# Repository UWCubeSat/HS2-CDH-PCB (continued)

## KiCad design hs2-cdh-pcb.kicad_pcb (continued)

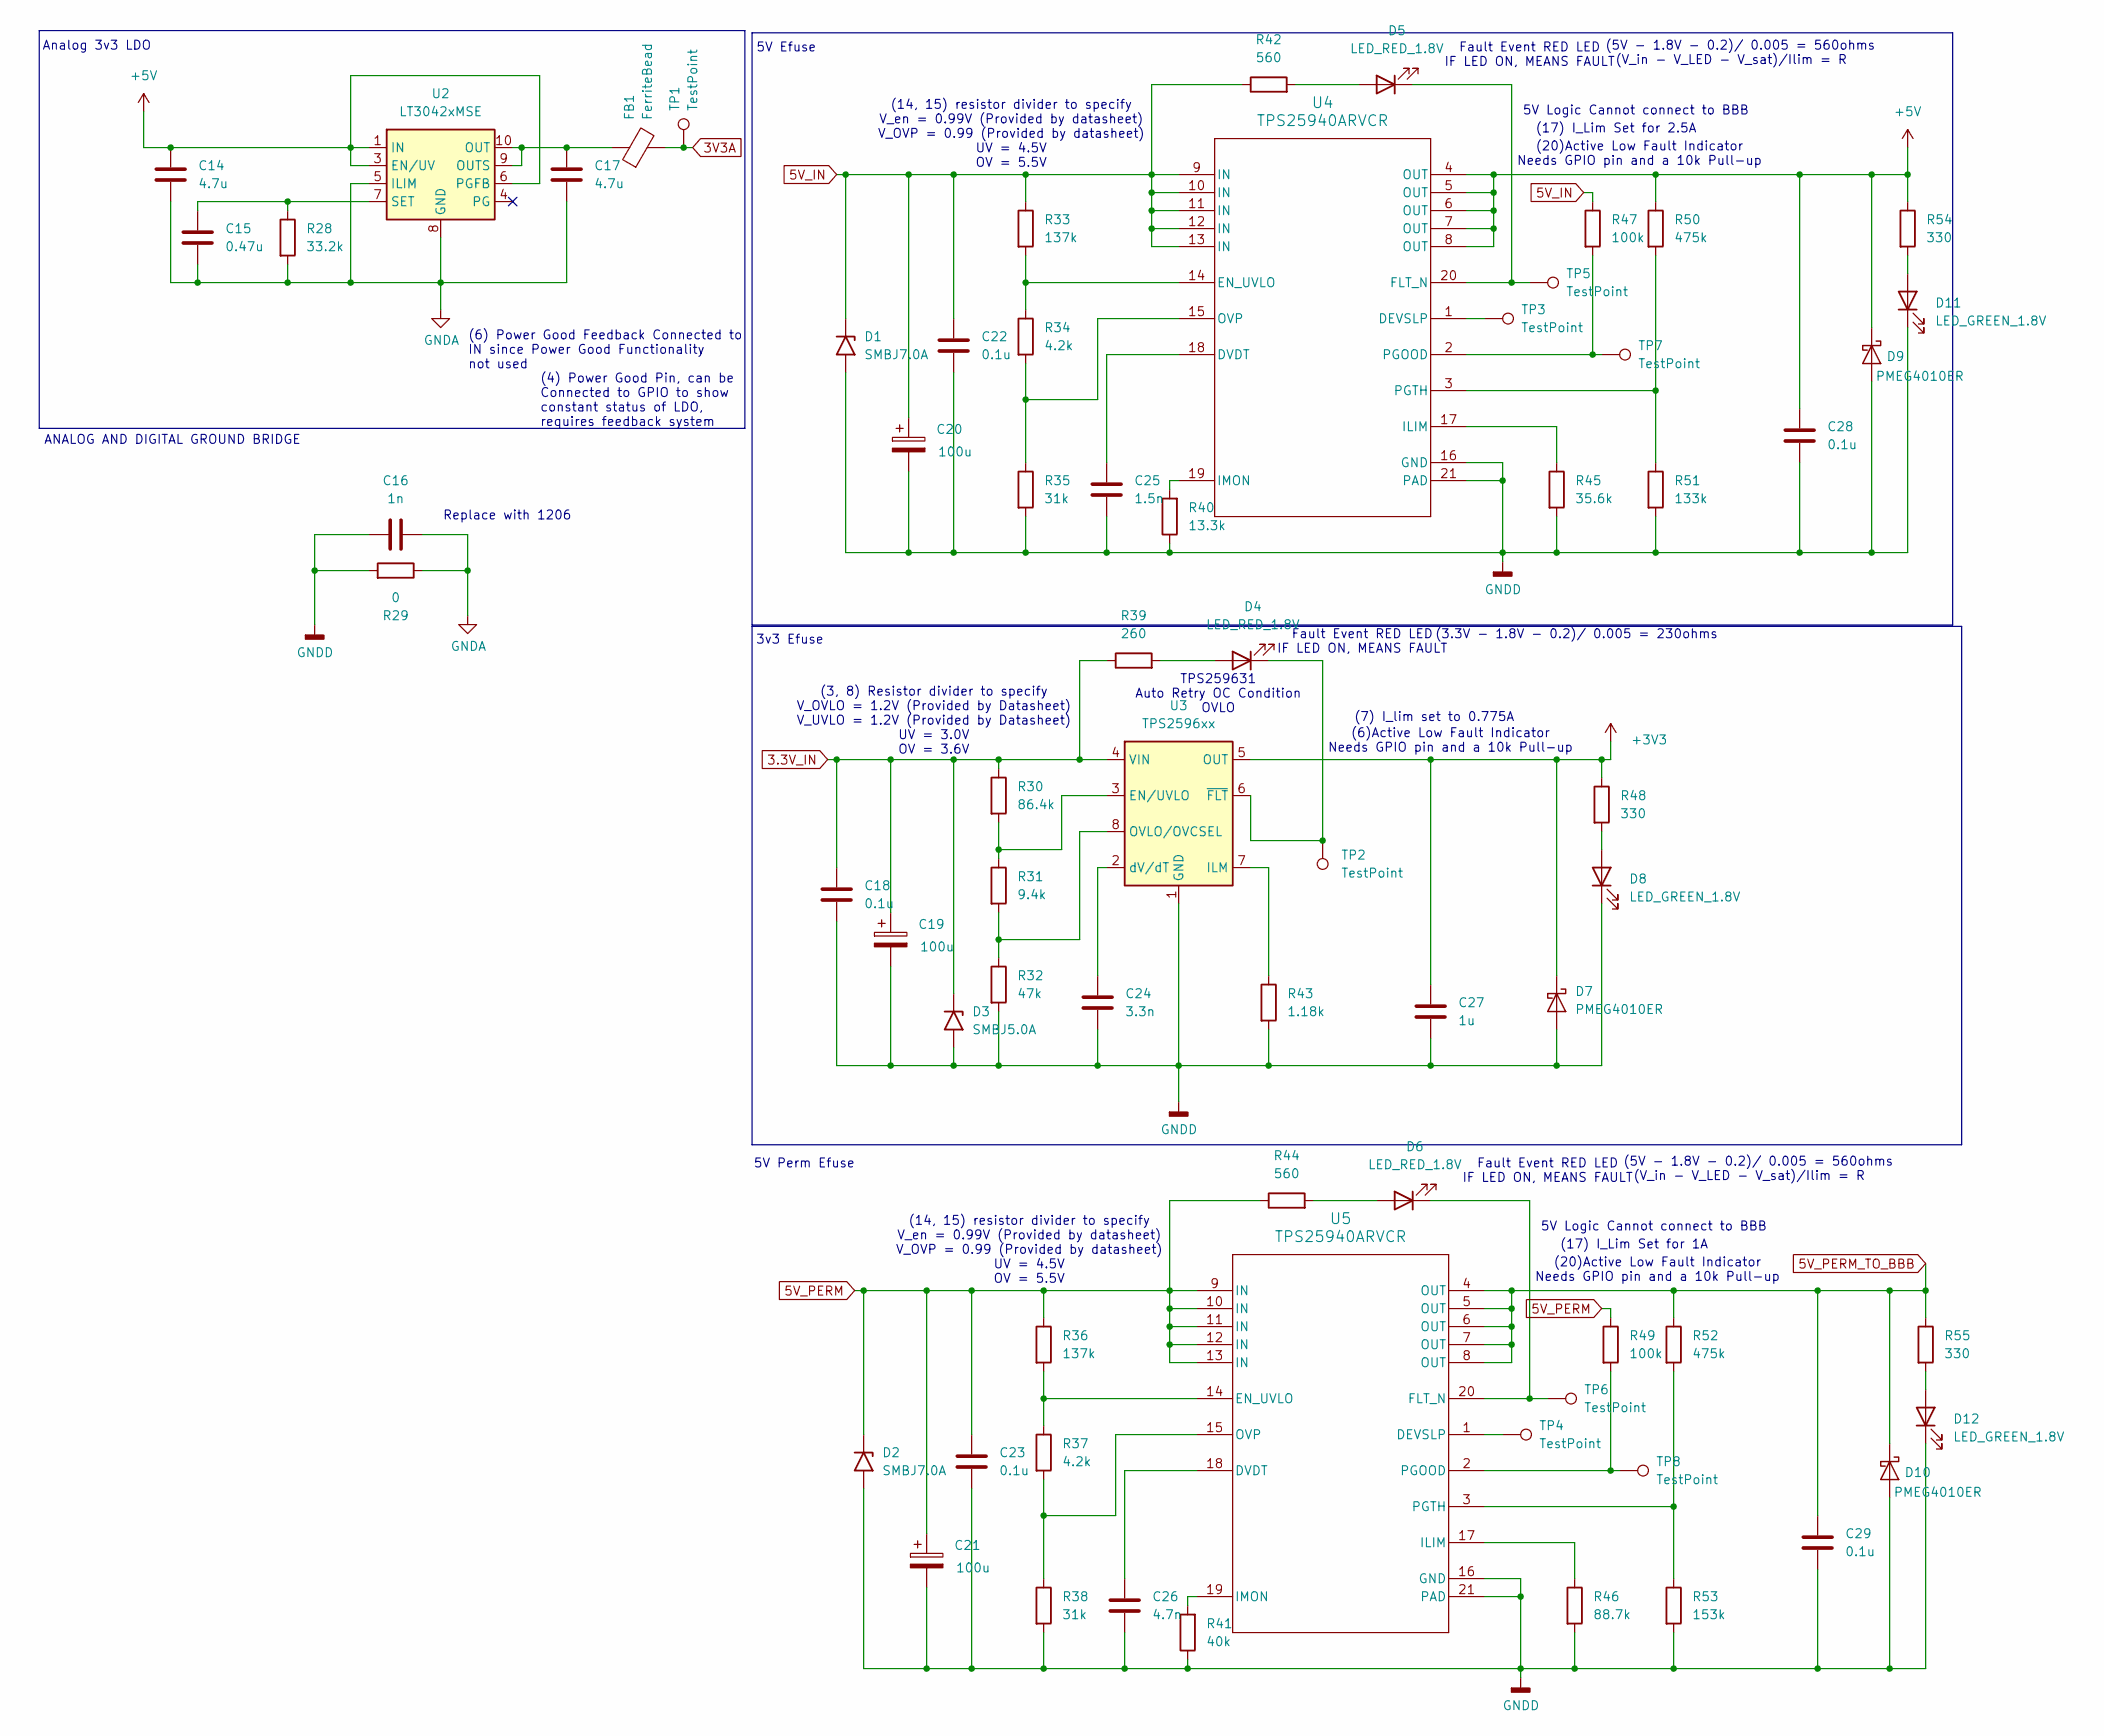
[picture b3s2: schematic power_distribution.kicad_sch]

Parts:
C14, C17: 4.7u; C_0603_1608Metric
C15: 0.47u; C_0603_1608Metric
C16: 1n; C_1206_3216Metric
C18, C22, C23, C28, C29: 0.1u; C_0603_1608Metric
C19, C20, C21: 100u; CAPMP7.6X4.3_1.9N_KEM
C24: 3.3n; C_0603_1608Metric
C25: 1.5n; C_0603_1608Metric
C26: 4.7n; C_0603_1608Metric
C27: 1u; C_0603_1608Metric
D1, D2: SMBJ7.0A; D_SMA
D3: SMBJ5.0A; D_SMA
D4, D5, D6: LED_RED_1.8V; LED_0603_1608Metric
D7, D9, D10: PMEG4010ER; Nexperia_CFP3_SOD-123W
D8, D11, D12: LED_GREEN_1.8V; LED_0603_1608Metric
FB1: FerriteBead; L_0603_1608Metric
R28: 33.2k; R_0603_1608Metric
R29: 0; R_1206_3216Metric
R30: 86.4k; R_0603_1608Metric
R31: 9.4k; R_0603_1608Metric
R32: 47k; R_0603_1608Metric
R33, R36: 137k; R_0603_1608Metric
R34, R37: 4.2k; R_0603_1608Metric
R35, R38: 31k; R_0603_1608Metric
R39: 260; R_0603_1608Metric
R40: 13.3k; R_0603_1608Metric
R41: 40k; R_0603_1608Metric
R42, R44: 560; R_0603_1608Metric
R43: 1.18k; R_0603_1608Metric
R45: 35.6k; R_0603_1608Metric
R46: 88.7k; R_0603_1608Metric
R47, R49: 100k; R_0603_1608Metric
R48, R54, R55: 330; R_0603_1608Metric
R50, R52: 475k; R_0603_1608Metric
R51: 133k; R_0603_1608Metric
R53: 153k; R_0603_1608Metric
TP1, TP2, TP3, TP4, TP5, TP6, TP7, TP8: TestPoint; TestPoint_Pad_D1.0mm
U2: LT3042xMSE; MSOP-10-1EP_3x3mm_P0.5mm_EP1.68x1.88mm
U3: TPS2596xx; TI_SO-PowerPAD-8_ThermalVias
U4, U5: TPS25940ARVCR; Texas_RVC0020A_WQFN-20-1EP_3x4mm_P0.5mm_EP1.6x2.6mm

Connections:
3.3V_IN: C18.1, C19.1, D3.1 (A1), R30.1, R39.1, U3.4 (VIN); also elsewhere on the board
3V3A: FB1.2, TP1.1 (1_1); also elsewhere on the board
5V_IN: C20.1, C22.1, D1.1 (A1), R33.1, R42.1, R47.1, U4.9 (IN), U4.10 (IN), U4.11 (IN), U4.12 (IN), U4.13 (IN); also elsewhere on the board
5V_PERM: C21.1, C23.1, D2.1 (A1), R36.1, R44.1, R49.1, U5.9 (IN), U5.10 (IN), U5.11 (IN), U5.12 (IN), U5.13 (IN); also elsewhere on the board
5V_PERM_TO_BBB: C29.1, D10.1 (K), R52.1, R55.1, U5.4 (OUT), U5.5 (OUT), U5.6 (OUT), U5.7 (OUT), U5.8 (OUT); also elsewhere on the board
+3V3: C27.1, D7.1 (K), R48.1, U3.5 (OUT); also elsewhere on the board
+5V: C14.1, C28.1, D9.1 (K), R50.1, R54.1, U2.1 (IN), U2.2 (IN), U2.3 (EN/UV), U2.6 (PGFB), U4.4 (OUT), U4.5 (OUT), U4.6 (OUT), U4.7 (OUT), U4.8 (OUT); also elsewhere on the board
GNDA: C14.2, C15.2, C16.2, C17.2, R28.2, R29.1, U2.5 (ILIM), U2.8 (GND), U2.11 (GND); also elsewhere on the board
GNDD: C16.1, C18.2, C19.2, C20.2, C21.2, C22.2, C23.2, C24.2, C25.2, C26.2, C27.2, C28.2, C29.2, D1.2 (A2), D2.2 (A2), D3.2 (A2), D7.2 (A), D8.1 (K), D9.2 (A), D10.2 (A), D11.1 (K), D12.1 (K), R29.2, R32.2, R35.2, R38.2, R40.1, R41.1, R43.2, R45.2, R46.2, R51.2, R53.2, U3.1 (GND), U3.9 (GND), U4.16 (GND), U4.21 (PAD), U5.16 (GND), U5.21 (PAD); also elsewhere on the board
unnamed: D4.2 (A), R39.2
unnamed: D4.1 (K), TP2.1 (1_1), U3.6 (~FLT)
unnamed: D5.2 (A), R42.2
unnamed: D5.1 (K), TP5.1 (1_1), U4.20 (FLT_N)
unnamed: D6.2 (A), R44.2
unnamed: D6.1 (K), TP6.1 (1_1), U5.20 (FLT_N)
unnamed: D8.2 (A), R48.2
unnamed: D11.2 (A), R54.2
unnamed: D12.2 (A), R55.2
unnamed: C17.1, FB1.1, U2.9 (OUTS), U2.10 (OUT)
unnamed: C15.1, R28.1, U2.7 (SET)
unnamed: R30.2, R31.1, U3.3 (EN/UVLO)
unnamed: R43.1, U3.7 (ILM)
unnamed: R31.2, R32.1, U3.8 (OVLO/OVCSEL)
unnamed: C24.1, U3.2 (dV/dT)
unnamed: TP3.1 (1_1), U4.1 (DEVSLP)
unnamed: C25.1, U4.18 (DVDT)
unnamed: R33.2, R34.1, U4.14 (EN_UVLO)
unnamed: R45.1, U4.17 (ILIM)
unnamed: R40.2, U4.19 (IMON)
unnamed: R34.2, R35.1, U4.15 (OVP)
unnamed: R47.2, TP7.1 (1_1), U4.2 (PGOOD)
unnamed: R50.2, R51.1, U4.3 (PGTH)
unnamed: TP4.1 (1_1), U5.1 (DEVSLP)
unnamed: C26.1, U5.18 (DVDT)
unnamed: R36.2, R37.1, U5.14 (EN_UVLO)
unnamed: R46.1, U5.17 (ILIM)
unnamed: R41.2, U5.19 (IMON)
unnamed: R37.2, R38.1, U5.15 (OVP)
unnamed: R49.2, TP8.1 (1_1), U5.2 (PGOOD)
unnamed: R52.2, R53.1, U5.3 (PGTH)

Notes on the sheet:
Fault Event RED LED IF LED ON, MEANS FAULT
(20)Active Low Fault Indicator Needs GPIO pin and a 10k Pull-up
(V_in - V_LED - V_sat)/Ilim = R
(3, 8) Resistor divider to specify V_OVLO = 1.2V (Provided by Datasheet) V_UVLO = 1.2V (Provided by Datasheet) UV = 3.0V OV = 3.6V
(5V - 1.8V - 0.2)/ 0.005 = 560ohms
Replace with 1206
5V Perm Efuse
(4) Power Good Pin, can be Connected to GPIO to show constant status of LDO, requires feedback system
(14, 15) resistor divider to specify V_en = 0.99V (Provided by datasheet) V_OVP = 0.99 (Provided by datasheet) UV = 4.5V OV = 5.5V
ANALOG AND DIGITAL GROUND BRIDGE
(6)Active Low Fault Indicator Needs GPIO pin and a 10k Pull-up
3v3 Efuse
(17) I_Lim Set for 2.5A
5V Logic Cannot connect to BBB
(3.3V - 1.8V - 0.2)/ 0.005 = 230ohms
Analog 3v3 LDO
(7) I_lim set to 0.775A
TPS259631 Auto Retry OC Condition OVLO
5V Efuse
(6) Power Good Feedback Connected to IN since Power Good Functionality not used
(17) I_Lim Set for 1A

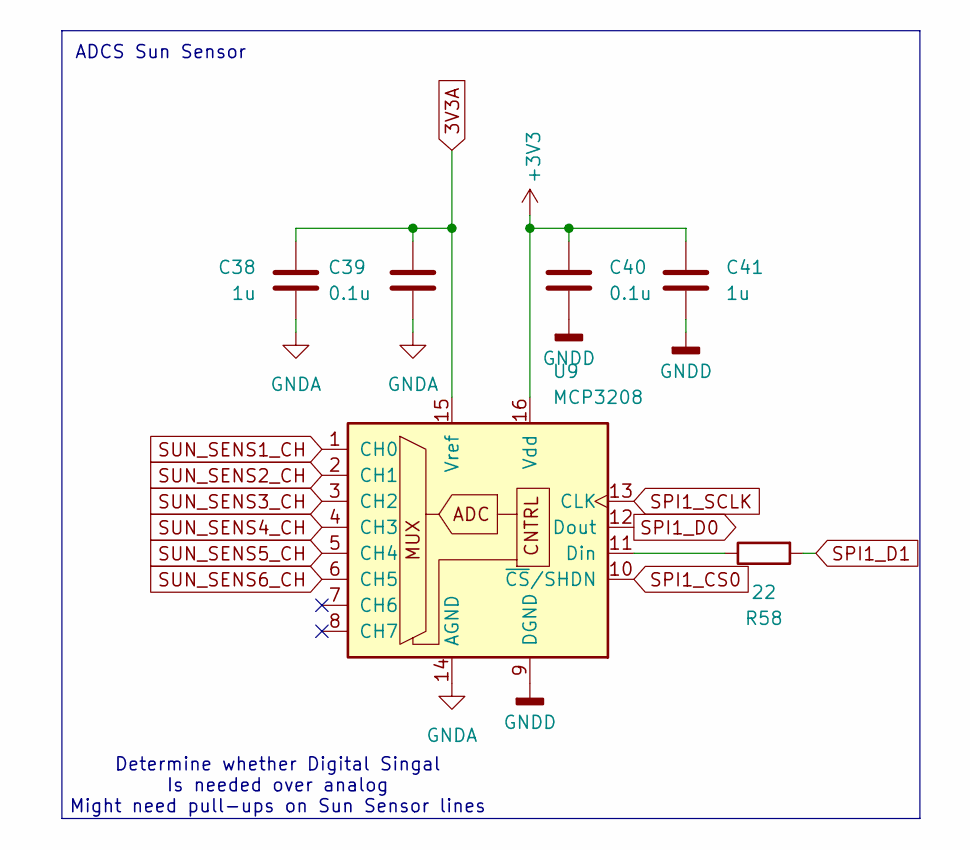
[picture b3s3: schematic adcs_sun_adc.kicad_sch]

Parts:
C38, C41: 1u; C_0603_1608Metric
C39, C40: 0.1u; C_0603_1608Metric
R58: 22; R_0603_1608Metric
U9: MCP3208; SOIC-16_3.9x9.9mm_P1.27mm

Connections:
3V3A: C38.1, C39.1, U9.15 (Vref); also elsewhere on the board
+3V3: C40.1, C41.1, U9.16 (Vdd); also elsewhere on the board
GNDA: C38.2, C39.2, U9.14 (AGND); also elsewhere on the board
GNDD: C40.2, C41.2, U9.9 (DGND); also elsewhere on the board
unnamed: R58.1, U9.11 (Din)
SPI1_CS0: U9.10 (~CS/SHDN); also elsewhere on the board
SPI1_D0: U9.12 (Dout); also elsewhere on the board
SPI1_D1: R58.2; also elsewhere on the board
SPI1_SCLK: U9.13 (CLK); also elsewhere on the board
SUN_SENS1_CH: U9.1 (CH0); also elsewhere on the board
SUN_SENS2_CH: U9.2 (CH1); also elsewhere on the board
SUN_SENS3_CH: U9.3 (CH2); also elsewhere on the board
SUN_SENS4_CH: U9.4 (CH3); also elsewhere on the board
SUN_SENS5_CH: U9.5 (CH4); also elsewhere on the board
SUN_SENS6_CH: U9.6 (CH5); also elsewhere on the board

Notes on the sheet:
Determine whether Digital Singal Is needed over analog Might need pull-ups on Sun Sensor lines
ADCS Sun Sensor

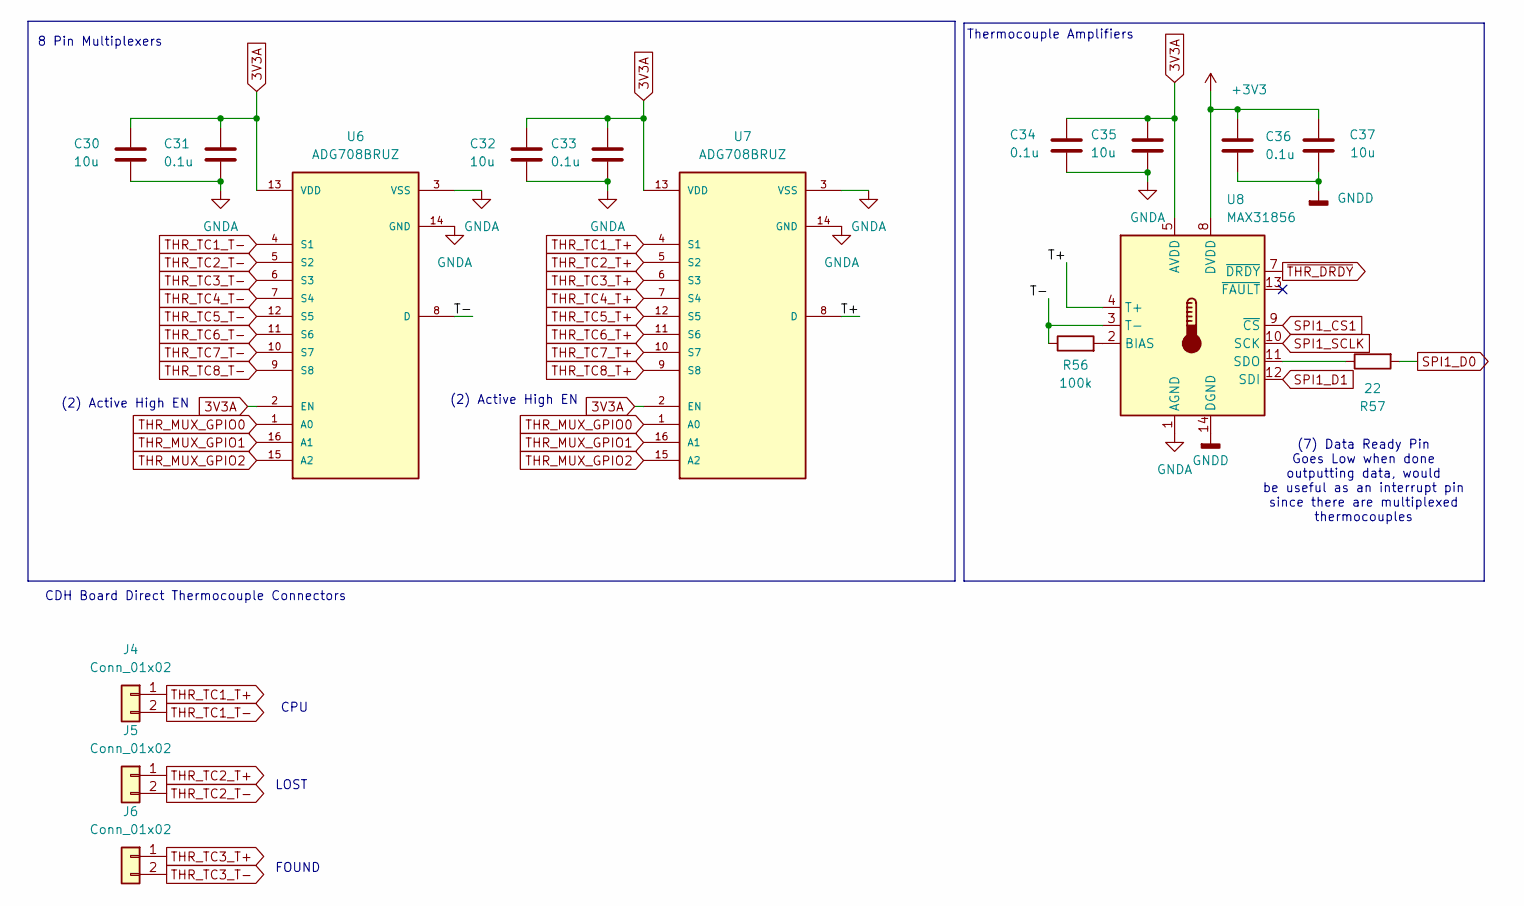
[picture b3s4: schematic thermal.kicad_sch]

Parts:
C30, C32, C35, C37: 10u; C_0603_1608Metric
C31, C33, C34, C36: 0.1u; C_0603_1608Metric
J4, J5, J6: Conn_01x02; JST_PH_S2B-PH-K_1x02_P2.00mm_Horizontal
R56: 100k; R_0603_1608Metric
R57: 22; R_0603_1608Metric
U6, U7: ADG708BRUZ; TSSOP16
U8: MAX31856; TSSOP-14_4.4x5mm_P0.65mm

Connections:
3V3A: C30.1, C31.1, C32.1, C33.1, C34.1, C35.1, U6.2 (EN), U6.13 (VDD), U7.2 (EN), U7.13 (VDD), U8.5 (AVDD); also elsewhere on the board
+3V3: C36.1, C37.1, U8.8 (DVDD); also elsewhere on the board
/thermal/T+: U7.8 (D), U8.4 (T+)
/thermal/T-: R56.1, U6.8 (D), U8.3 (T-)
GNDA: C30.2, C31.2, C32.2, C33.2, C34.2, C35.2, U6.3 (VSS), U6.14 (GND), U7.3 (VSS), U7.14 (GND), U8.1 (AGND); also elsewhere on the board
GNDD: C36.2, C37.2, U8.14 (DGND); also elsewhere on the board
unnamed: R56.2, U8.2 (BIAS)
unnamed: R57.1, U8.11 (SDO)
SPI1_CS1: U8.9 (~CS); also elsewhere on the board
SPI1_D0: R57.2; also elsewhere on the board
SPI1_D1: U8.12 (SDI); also elsewhere on the board
SPI1_SCLK: U8.10 (SCK); also elsewhere on the board
THR_MUX_GPIO0: U6.1 (A0), U7.1 (A0); also elsewhere on the board
THR_MUX_GPIO1: U6.16 (A1), U7.16 (A1); also elsewhere on the board
THR_MUX_GPIO2: U6.15 (A2), U7.15 (A2); also elsewhere on the board
THR_TC1_T+: J4.1, U7.4 (S1)
THR_TC1_T-: J4.2, U6.4 (S1)
THR_TC2_T+: J5.1, U7.5 (S2)
THR_TC2_T-: J5.2, U6.5 (S2)
THR_TC3_T+: J6.1, U7.6 (S3)
THR_TC3_T-: J6.2, U6.6 (S3)
THR_TC4_T+: U7.7 (S4); also elsewhere on the board
THR_TC4_T-: U6.7 (S4); also elsewhere on the board
THR_TC5_T+: U7.12 (S5); also elsewhere on the board
THR_TC5_T-: U6.12 (S5); also elsewhere on the board
THR_TC6_T+: U7.11 (S6); also elsewhere on the board
THR_TC6_T-: U6.11 (S6); also elsewhere on the board
THR_TC7_T+: U7.10 (S7); also elsewhere on the board
THR_TC7_T-: U6.10 (S7); also elsewhere on the board
THR_TC8_T+: U7.9 (S8); also elsewhere on the board
THR_TC8_T-: U6.9 (S8); also elsewhere on the board
~THR_DRDY: U8.7 (~DRDY); also elsewhere on the board

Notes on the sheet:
LOST
CDH Board Direct Thermocouple Connectors
FOUND
(2) Active High EN
(7) Data Ready Pin Goes Low when done outputting data, would be useful as an interrupt pin since there are multiplexed thermocouples
CPU
8 Pin Multiplexers
Thermocouple Amplifiers

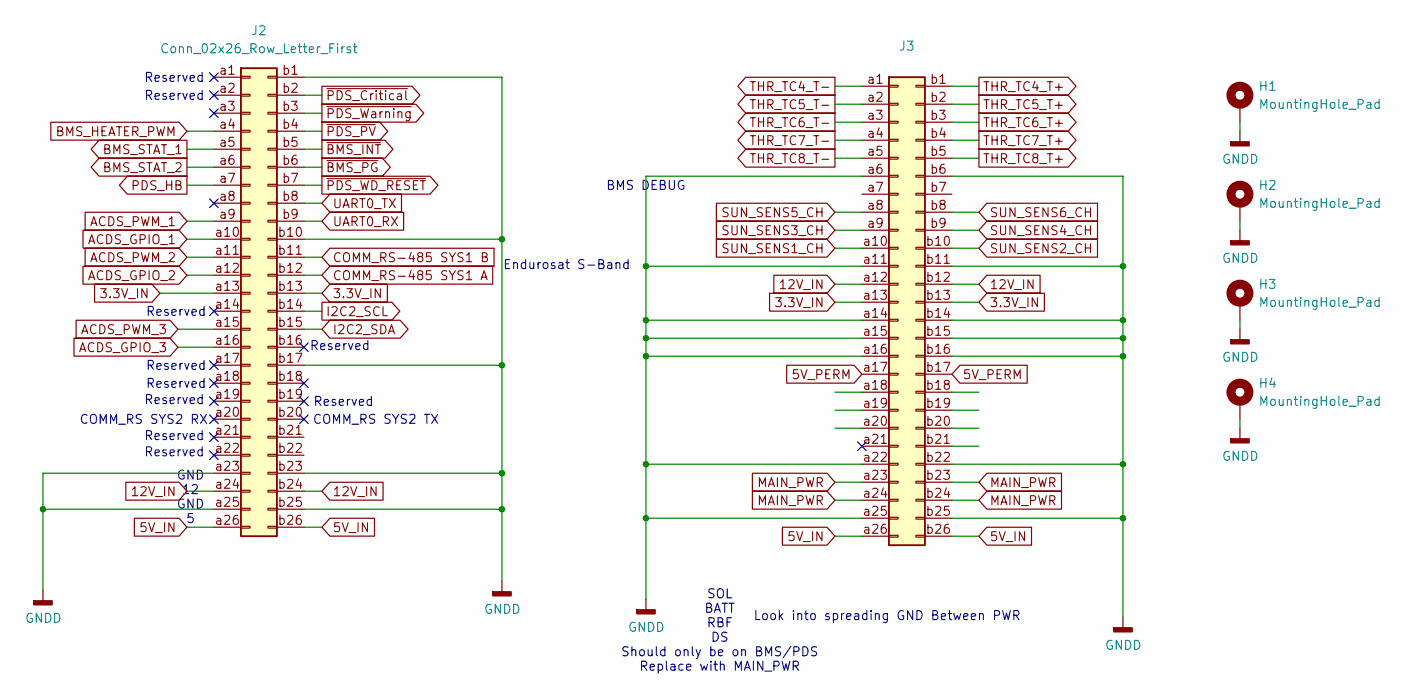
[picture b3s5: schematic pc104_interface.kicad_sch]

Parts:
H1, H2, H3, H4: MountingHole_Pad; MountingHole_3.2mm_M3_Pad
J2, J3: Conn_02x26_Row_Letter_First; PinSocket_2x26_P2.54mm_Vertical

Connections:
3.3V_IN: J2.a13, J2.b13, J3.a13, J3.b13; also elsewhere on the board
5V_IN: J2.a26, J2.b26, J3.a26, J3.b26; also elsewhere on the board
5V_PERM: J3.a17, J3.b17; also elsewhere on the board
12V_IN: J2.a24, J2.b24, J3.a12, J3.b12
ACDS_GPIO_1: J2.a10; also elsewhere on the board
ACDS_GPIO_2: J2.a12; also elsewhere on the board
ACDS_GPIO_3: J2.a16; also elsewhere on the board
ACDS_PWM_1: J2.a9; also elsewhere on the board
ACDS_PWM_2: J2.a11; also elsewhere on the board
ACDS_PWM_3: J2.a15; also elsewhere on the board
BMS_HEATER_PWM: J2.a4; also elsewhere on the board
BMS_STAT_1: J2.a5; also elsewhere on the board
BMS_STAT_2: J2.a6; also elsewhere on the board
COMM_RS-485 SYS1 A: J2.b12; also elsewhere on the board
COMM_RS-485 SYS1 B: J2.b11; also elsewhere on the board
GNDD: H1.1 (1_1), H2.1 (1_1), H3.1 (1_1), H4.1 (1_1), J2.a23, J2.a25, J2.b1, J2.b10, J2.b17, J2.b23, J2.b25, J3.a6, J3.a11, J3.a14, J3.a15, J3.a16, J3.a22, J3.a25, J3.b6, J3.b11, J3.b14, J3.b15, J3.b16, J3.b22, J3.b25; also elsewhere on the board
I2C2_SCL: J2.b14; also elsewhere on the board
I2C2_SDA: J2.b15; also elsewhere on the board
MAIN_PWR: J3.a23, J3.a24, J3.b23, J3.b24
PDS_HB: J2.a7; also elsewhere on the board
SUN_SENS1_CH: J3.a10; also elsewhere on the board
SUN_SENS2_CH: J3.b10; also elsewhere on the board
SUN_SENS3_CH: J3.a9; also elsewhere on the board
SUN_SENS4_CH: J3.b9; also elsewhere on the board
SUN_SENS5_CH: J3.a8; also elsewhere on the board
SUN_SENS6_CH: J3.b8; also elsewhere on the board
THR_TC4_T+: J3.b1; also elsewhere on the board
THR_TC4_T-: J3.a1; also elsewhere on the board
THR_TC5_T+: J3.b2; also elsewhere on the board
THR_TC5_T-: J3.a2; also elsewhere on the board
THR_TC6_T+: J3.b3; also elsewhere on the board
THR_TC6_T-: J3.a3; also elsewhere on the board
THR_TC7_T+: J3.b4; also elsewhere on the board
THR_TC7_T-: J3.a4; also elsewhere on the board
THR_TC8_T+: J3.b5; also elsewhere on the board
THR_TC8_T-: J3.a5; also elsewhere on the board
UART0_RX: J2.b9; also elsewhere on the board
UART0_TX: J2.b8; also elsewhere on the board
~BMS_INT: J2.b5; also elsewhere on the board
~BMS_PG: J2.b6; also elsewhere on the board
~PDS_Critical: J2.b2; also elsewhere on the board
~PDS_PV: J2.b4; also elsewhere on the board
~PDS_WD_RESET: J2.b7; also elsewhere on the board
~PDS_Warning: J2.b3; also elsewhere on the board

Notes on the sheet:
Reserved
COMM_RS SYS2 RX
SOL BATT RBF DS Should only be on BMS/PDS Replace with MAIN_PWR
Endurosat S-Band
GND 12 GND 5
Look into spreading GND Between PWR
COMM_RS SYS2 TX
BMS DEBUG

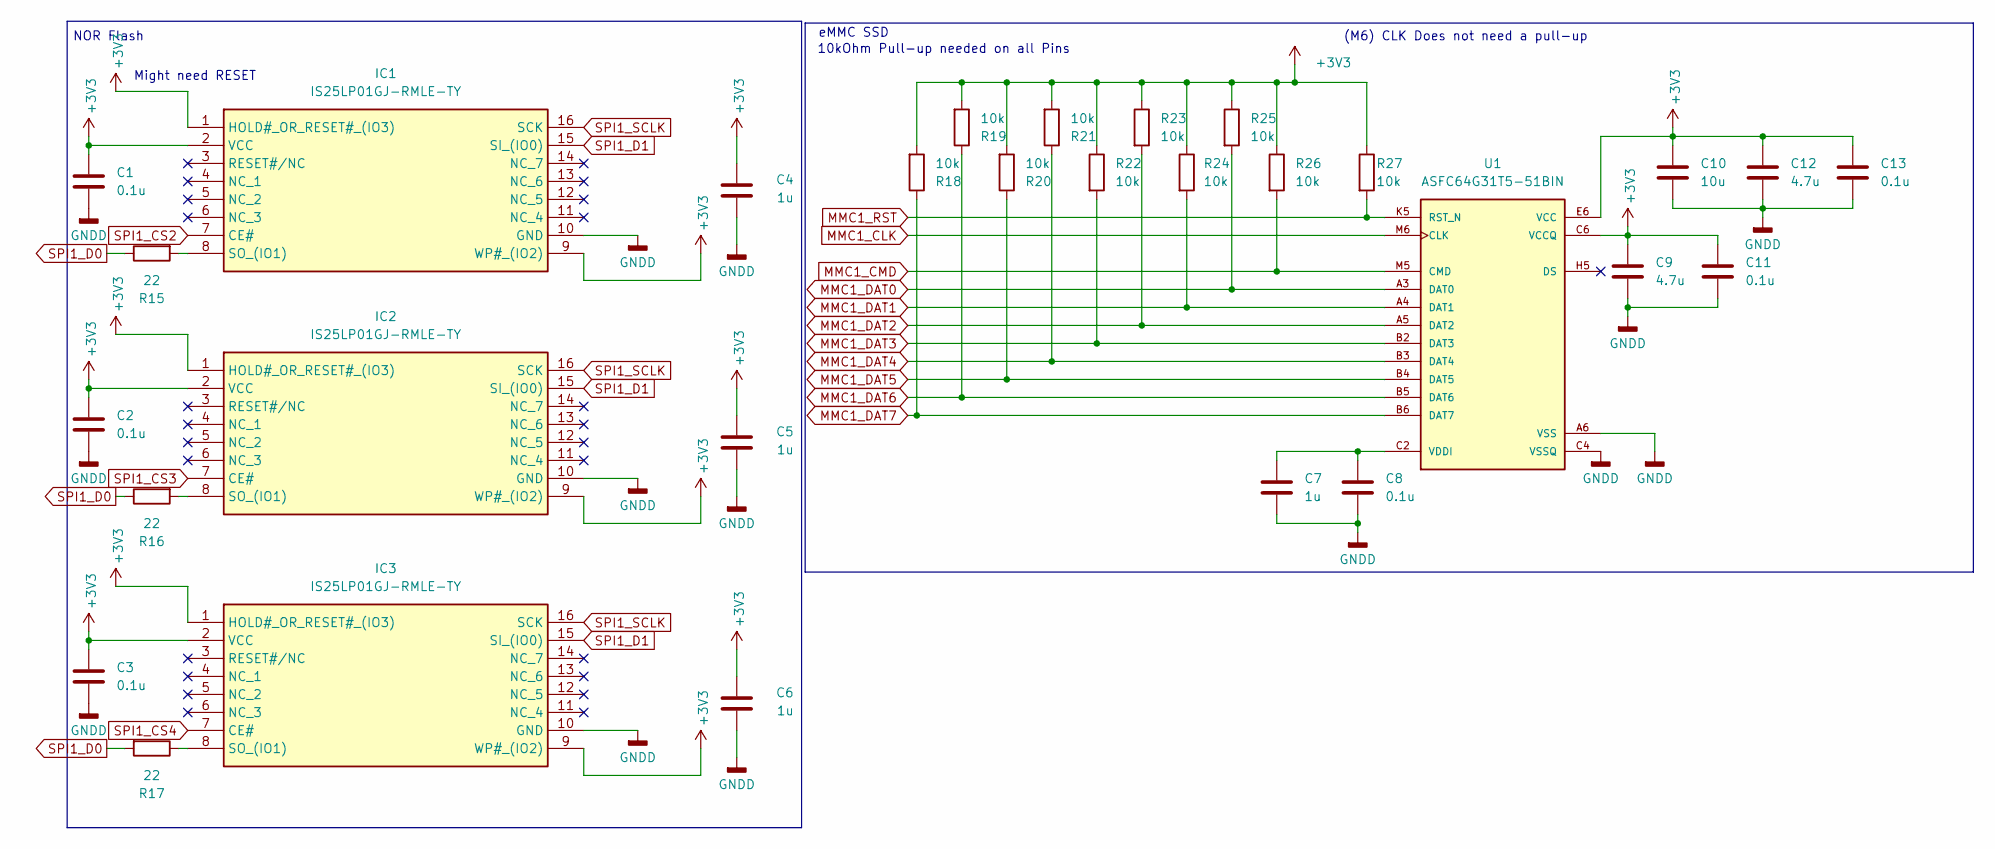
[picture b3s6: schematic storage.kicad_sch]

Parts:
C1, C2, C3, C8, C11, C13: 0.1u; C_0603_1608Metric
C4, C5, C6, C7: 1u; C_0603_1608Metric
C9, C12: 4.7u; C_0603_1608Metric
C10: 10u; C_0603_1608Metric
IC1, IC2, IC3: IS25LP01GJ-RMLE-TY; SOIC127P1032X265-16N; Manufacturer_Part_Number IS25LP01GJ-RMLE-TY
R15, R16, R17: 22; R_0603_1608Metric
R18, R19, R20, R21, R22, R23, R24, R25, R26, R27: 10k; R_0603_1608Metric
U1: ASFC64G31T5-51BIN; LFBGA-153_11.5x13mm_Layout14x14_P0.5mm

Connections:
+3V3: C1.1, C2.1, C3.1, C4.1, C5.1, C6.1, C9.1, C10.1, C11.1, C12.1, C13.1, IC1.1 (HOLD#_OR_RESET#_(IO3)), IC1.2 (VCC), IC1.9 (WP#_(IO2)), IC2.1 (HOLD#_OR_RESET#_(IO3)), IC2.2 (VCC), IC2.9 (WP#_(IO2)), IC3.1 (HOLD#_OR_RESET#_(IO3)), IC3.2 (VCC), IC3.9 (WP#_(IO2)), R18.2, R19.2, R20.2, R21.2, R22.1, R23.1, R24.1, R25.1, R26.1, R27.1, U1.C6 (VCCQ), U1.E6 (VCC), U1.F5 (VCC), U1.J10 (VCC), U1.K9 (VCC), U1.M4 (VCCQ), U1.N4 (VCCQ), U1.P3 (VCCQ), U1.P5 (VCCQ); also elsewhere on the board
GNDD: C1.2, C2.2, C3.2, C4.2, C5.2, C6.2, C7.2, C8.2, C9.2, C10.2, C11.2, C12.2, C13.2, IC1.10 (GND), IC2.10 (GND), IC3.10 (GND), U1.A6 (VSS), U1.C4 (VSSQ), U1.E7 (VSS), U1.G5 (VSS), U1.H10 (VSS), U1.J5 (VSS), U1.K8 (VSS), U1.N2 (VSSQ), U1.N5 (VSSQ), U1.P4 (VSSQ), U1.P6 (VSSQ); also elsewhere on the board
MMC1_CLK: U1.M6 (CLK); also elsewhere on the board
MMC1_CMD: R26.2, U1.M5 (CMD); also elsewhere on the board
MMC1_DAT0: R25.2, U1.A3 (DAT0); also elsewhere on the board
MMC1_DAT1: R24.2, U1.A4 (DAT1); also elsewhere on the board
MMC1_DAT2: R23.2, U1.A5 (DAT2); also elsewhere on the board
MMC1_DAT3: R22.2, U1.B2 (DAT3); also elsewhere on the board
MMC1_DAT4: R21.1, U1.B3 (DAT4); also elsewhere on the board
MMC1_DAT5: R20.1, U1.B4 (DAT5); also elsewhere on the board
MMC1_DAT6: R19.1, U1.B5 (DAT6); also elsewhere on the board
MMC1_DAT7: R18.1, U1.B6 (DAT7); also elsewhere on the board
MMC1_RST: R27.2, U1.K5 (RST_N); also elsewhere on the board
unnamed: IC1.8 (SO_(IO1)), R15.2
unnamed: IC2.8 (SO_(IO1)), R16.2
unnamed: IC3.8 (SO_(IO1)), R17.1
unnamed: C7.1, C8.1, U1.C2 (VDDI)
SPI1_CS2: IC1.7 (CE#); also elsewhere on the board
SPI1_CS3: IC2.7 (CE#); also elsewhere on the board
SPI1_CS4: IC3.7 (CE#); also elsewhere on the board
SPI1_D0: R15.1, R16.1, R17.2; also elsewhere on the board
SPI1_D1: IC1.15 (SI_(IO0)), IC2.15 (SI_(IO0)), IC3.15 (SI_(IO0)); also elsewhere on the board
SPI1_SCLK: IC1.16 (SCK), IC2.16 (SCK), IC3.16 (SCK); also elsewhere on the board

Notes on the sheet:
(M6) CLK Does not need a pull-up
Might need RESET
eMMC SSD
10kOhm Pull-up needed on all Pins
NOR Flash

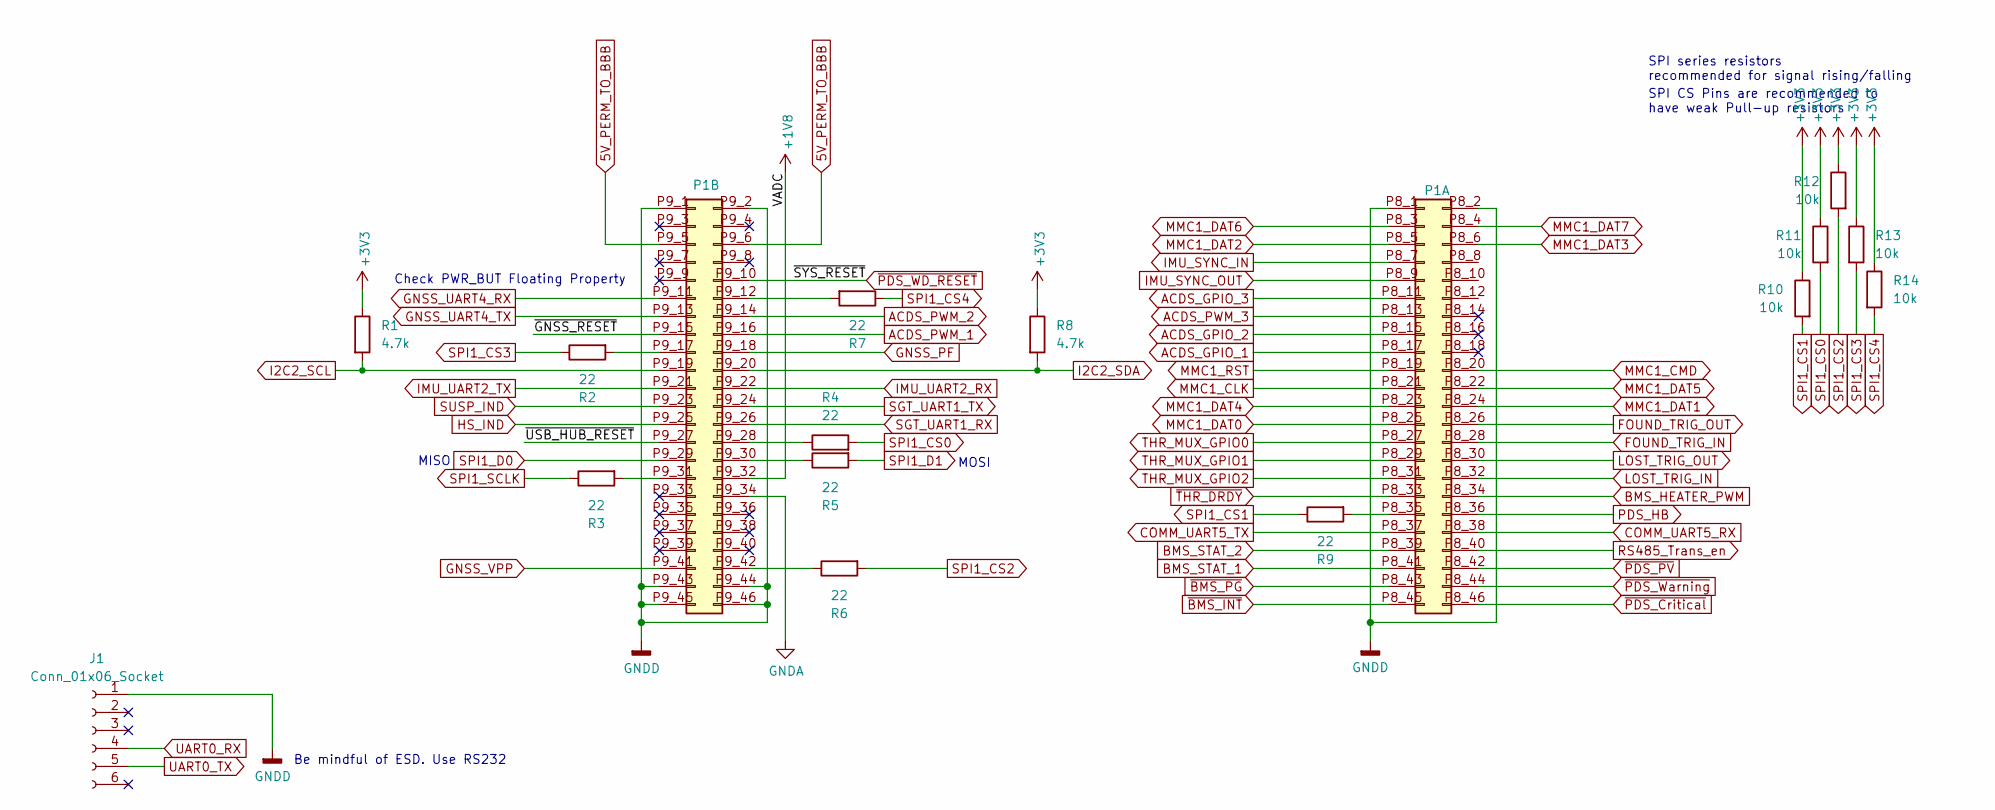
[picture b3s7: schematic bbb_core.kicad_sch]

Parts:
J1: Conn_01x06_Socket; PinSocket_1x06_P2.54mm_Vertical
P1: BBB_Cape
R1, R8: 4.7k; R_0603_1608Metric
R2, R3, R4, R5, R6, R7, R9: 22; R_0603_1608Metric
R10, R11, R12, R13, R14: 10k; R_0603_1608Metric

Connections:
5V_PERM_TO_BBB: P1.P9_5 (Pin_5), P1.P9_6 (Pin_6); also elsewhere on the board
+1V8: P1.P9_32 (Pin_32)
+3V3: R1.1, R8.1, R10.1, R11.1, R12.1, R13.1, R14.1; also elsewhere on the board
/bbb_core.kicad_sch/~GNSS_RESET: P1.P9_15 (Pin_15)
/bbb_core.kicad_sch/~USB_HUB_RESET: P1.P9_27 (Pin_27)
ACDS_GPIO_1: P1.P8_17 (Pin_17); also elsewhere on the board
ACDS_GPIO_2: P1.P8_15 (Pin_15); also elsewhere on the board
ACDS_GPIO_3: P1.P8_11 (Pin_11); also elsewhere on the board
ACDS_PWM_1: P1.P9_16 (Pin_16); also elsewhere on the board
ACDS_PWM_2: P1.P9_14 (Pin_14); also elsewhere on the board
ACDS_PWM_3: P1.P8_13 (Pin_13); also elsewhere on the board
BMS_HEATER_PWM: P1.P8_34 (Pin_34); also elsewhere on the board
BMS_STAT_1: P1.P8_41 (Pin_41); also elsewhere on the board
BMS_STAT_2: P1.P8_39 (Pin_39); also elsewhere on the board
COMM_UART5_RX: P1.P8_38 (Pin_38); also elsewhere on the board
COMM_UART5_TX: P1.P8_37 (Pin_37); also elsewhere on the board
FOUND_TRIG_IN: P1.P8_28 (Pin_28); also elsewhere on the board
FOUND_TRIG_OUT: P1.P8_26 (Pin_26); also elsewhere on the board
GNDA: P1.P9_34 (Pin_34); also elsewhere on the board
GNDD: J1.1, P1.P8_1 (Pin_1), P1.P8_2 (Pin_2), P1.P9_1 (Pin_1), P1.P9_2 (Pin_2), P1.P9_43 (Pin_43), P1.P9_44 (Pin_44), P1.P9_45 (Pin_45), P1.P9_46 (Pin_46); also elsewhere on the board
GNSS_PF: P1.P9_18 (Pin_18); also elsewhere on the board
GNSS_UART4_RX: P1.P9_11 (Pin_11); also elsewhere on the board
GNSS_UART4_TX: P1.P9_13 (Pin_13); also elsewhere on the board
GNSS_VPP: P1.P9_41 (Pin_41); also elsewhere on the board
HS_IND: P1.P9_25 (Pin_25); also elsewhere on the board
I2C2_SCL: P1.P9_19 (Pin_19), R1.2; also elsewhere on the board
I2C2_SDA: P1.P9_20 (Pin_20), R8.2; also elsewhere on the board
IMU_SYNC_IN: P1.P8_7 (Pin_7); also elsewhere on the board
IMU_SYNC_OUT: P1.P8_9 (Pin_9); also elsewhere on the board
IMU_UART2_RX: P1.P9_22 (Pin_22); also elsewhere on the board
IMU_UART2_TX: P1.P9_21 (Pin_21); also elsewhere on the board
LOST_TRIG_IN: P1.P8_32 (Pin_32); also elsewhere on the board
LOST_TRIG_OUT: P1.P8_30 (Pin_30); also elsewhere on the board
MMC1_CLK: P1.P8_21 (Pin_21); also elsewhere on the board
MMC1_CMD: P1.P8_20 (Pin_20); also elsewhere on the board
MMC1_DAT0: P1.P8_25 (Pin_25); also elsewhere on the board
MMC1_DAT1: P1.P8_24 (Pin_24); also elsewhere on the board
MMC1_DAT2: P1.P8_5 (Pin_5); also elsewhere on the board
MMC1_DAT3: P1.P8_6 (Pin_6); also elsewhere on the board
MMC1_DAT4: P1.P8_23 (Pin_23); also elsewhere on the board
MMC1_DAT5: P1.P8_22 (Pin_22); also elsewhere on the board
MMC1_DAT6: P1.P8_3 (Pin_3); also elsewhere on the board
MMC1_DAT7: P1.P8_4 (Pin_4); also elsewhere on the board
MMC1_RST: P1.P8_19 (Pin_19); also elsewhere on the board
unnamed: P1.P8_35 (Pin_35), R9.2
unnamed: P1.P9_12 (Pin_12), R7.2
unnamed: P1.P9_17 (Pin_17), R2.2
unnamed: P1.P9_28 (Pin_28), R4.1
unnamed: P1.P9_30 (Pin_30), R5.1
unnamed: P1.P9_31 (Pin_31), R3.2
unnamed: P1.P9_42 (Pin_42), R6.1
PDS_HB: P1.P8_36 (Pin_36); also elsewhere on the board
RS485_Trans_en: P1.P8_40 (Pin_40); also elsewhere on the board
SGT_UART1_RX: P1.P9_26 (Pin_26); also elsewhere on the board
SGT_UART1_TX: P1.P9_24 (Pin_24); also elsewhere on the board
SPI1_CS0: R4.2, R11.2; also elsewhere on the board
SPI1_CS1: R9.1, R10.2; also elsewhere on the board
SPI1_CS2: R6.2, R12.2; also elsewhere on the board
SPI1_CS3: R2.1, R13.2; also elsewhere on the board
SPI1_CS4: R7.1, R14.2; also elsewhere on the board
SPI1_D0: P1.P9_29 (Pin_29); also elsewhere on the board
SPI1_D1: R5.2; also elsewhere on the board
SPI1_SCLK: R3.1; also elsewhere on the board
SUSP_IND: P1.P9_23 (Pin_23); also elsewhere on the board
THR_MUX_GPIO0: P1.P8_27 (Pin_27); also elsewhere on the board
THR_MUX_GPIO1: P1.P8_29 (Pin_29); also elsewhere on the board
THR_MUX_GPIO2: P1.P8_31 (Pin_31); also elsewhere on the board
UART0_RX: J1.4; also elsewhere on the board
UART0_TX: J1.5; also elsewhere on the board
~BMS_INT: P1.P8_45 (Pin_45); also elsewhere on the board
~BMS_PG: P1.P8_43 (Pin_43); also elsewhere on the board
~PDS_Critical: P1.P8_46 (Pin_46); also elsewhere on the board
~PDS_PV: P1.P8_42 (Pin_42); also elsewhere on the board
~PDS_WD_RESET: P1.P9_10 (Pin_10); also elsewhere on the board
~PDS_Warning: P1.P8_44 (Pin_44); also elsewhere on the board
~THR_DRDY: P1.P8_33 (Pin_33); also elsewhere on the board

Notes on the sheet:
MISO
SPI CS Pins are recommended to have weak Pull-up resistors
Be mindful of ESD. Use RS232
Check PWR_BUT Floating Property
SPI series resistors recommended for signal rising/falling
MOSI
